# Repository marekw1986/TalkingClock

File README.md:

# TalkingClock

## Overwiev
This is repository of firmware for Talking Clock project. 
It uses vintage parts, such as WDC65C02 CPU, M6242B RTC, MC6840 timer or R65C51 UART. 
It also consists SP0256-AL2 chip, providing retro speach synthesis capability.

This project is still in development.

## Required tools
You need [cc65](https://github.com/cc65/cc65) to build this project.
Additionaly there are two PLD files, consisting descriptions of address decoders for GAL chips used in this project. 
To synthesise them you need [GalAsm](https://github.com/daveho/GALasm).

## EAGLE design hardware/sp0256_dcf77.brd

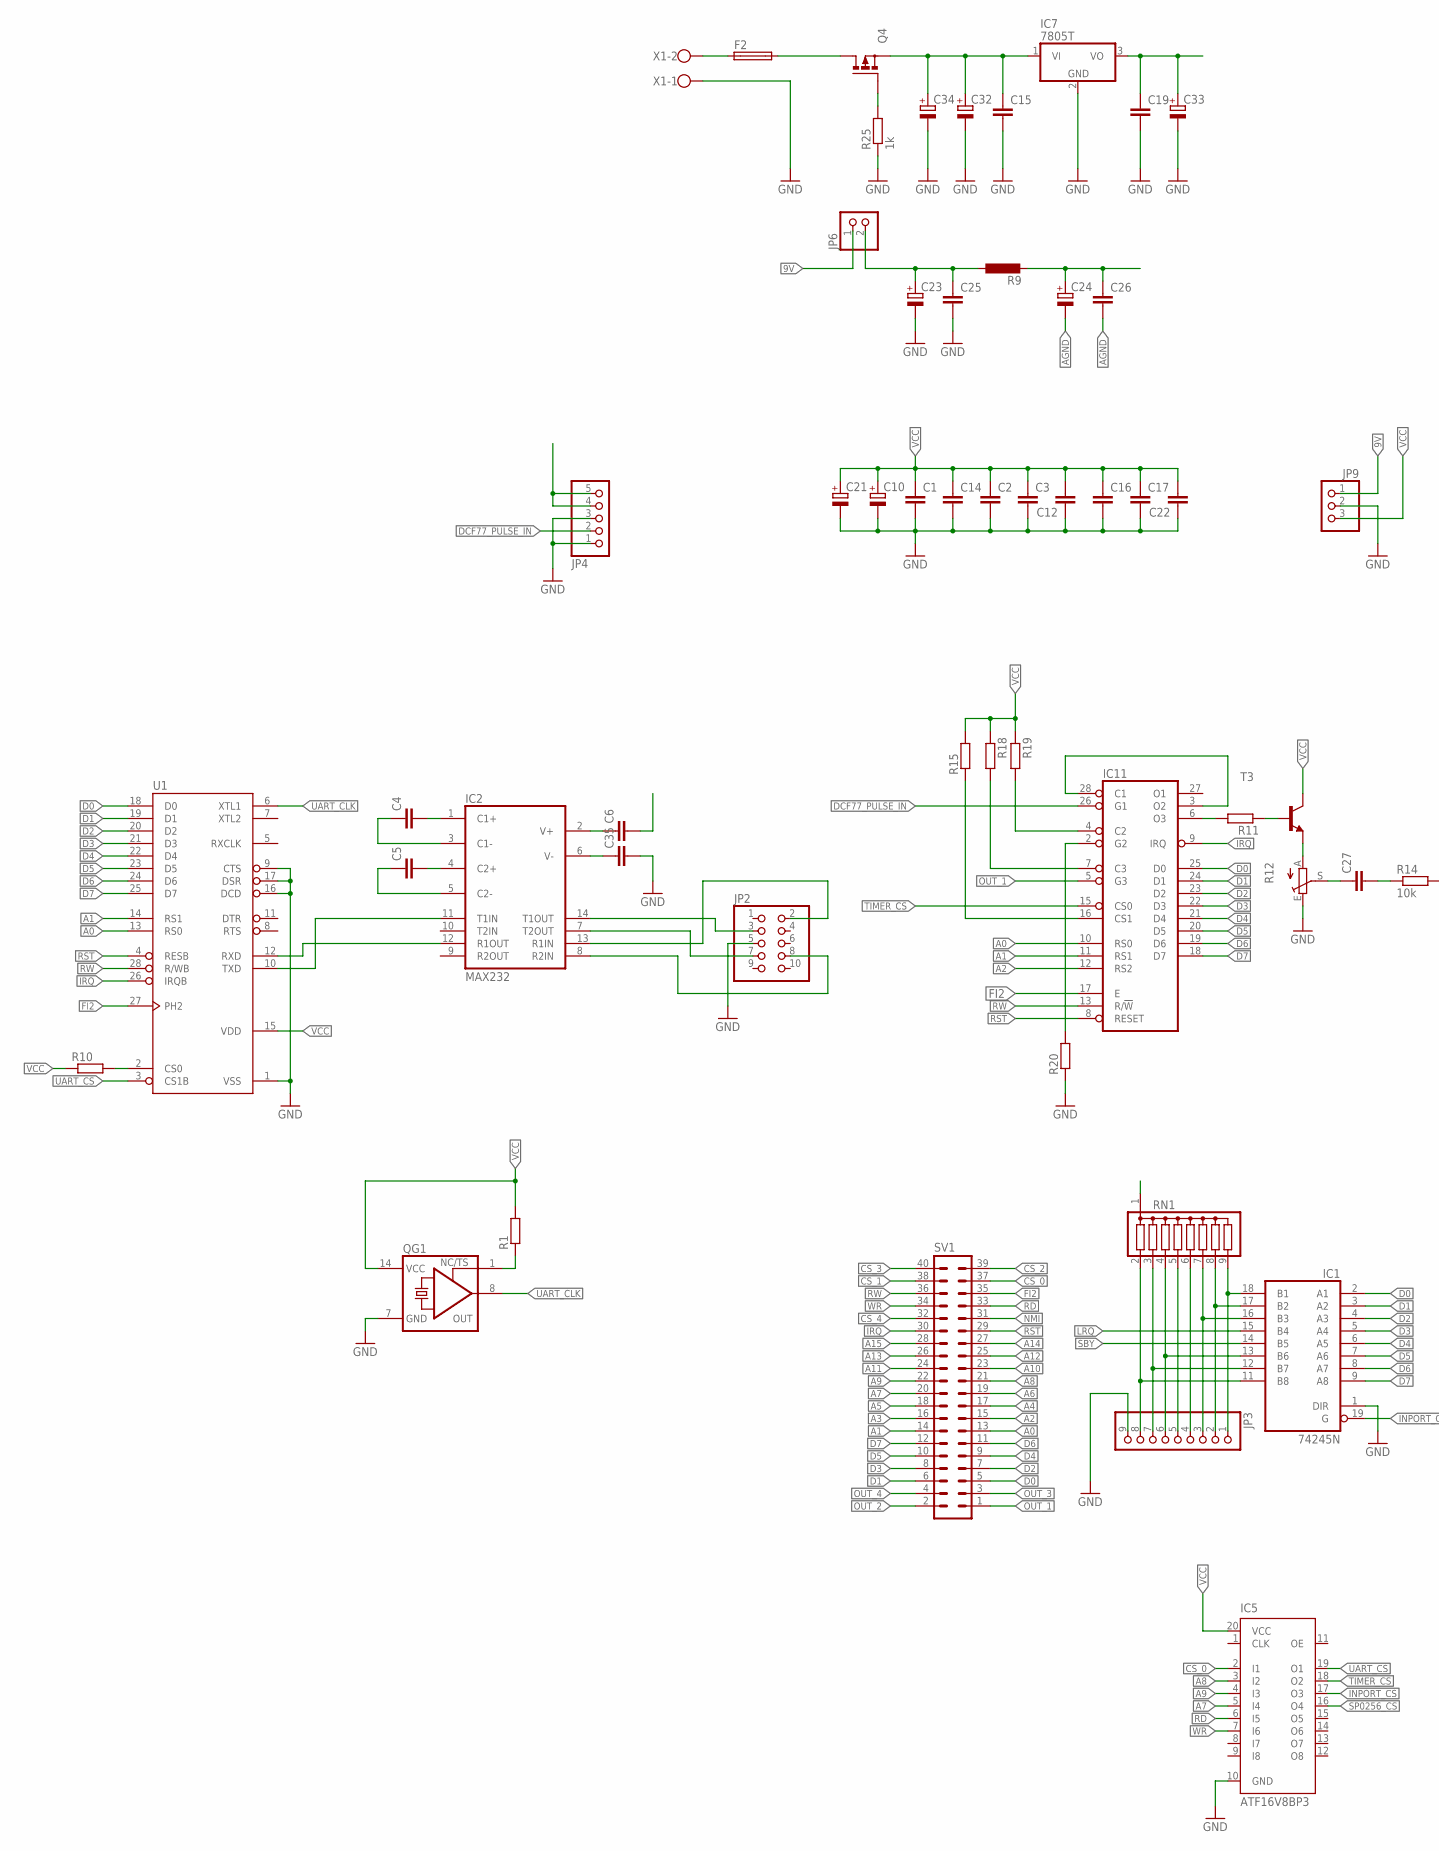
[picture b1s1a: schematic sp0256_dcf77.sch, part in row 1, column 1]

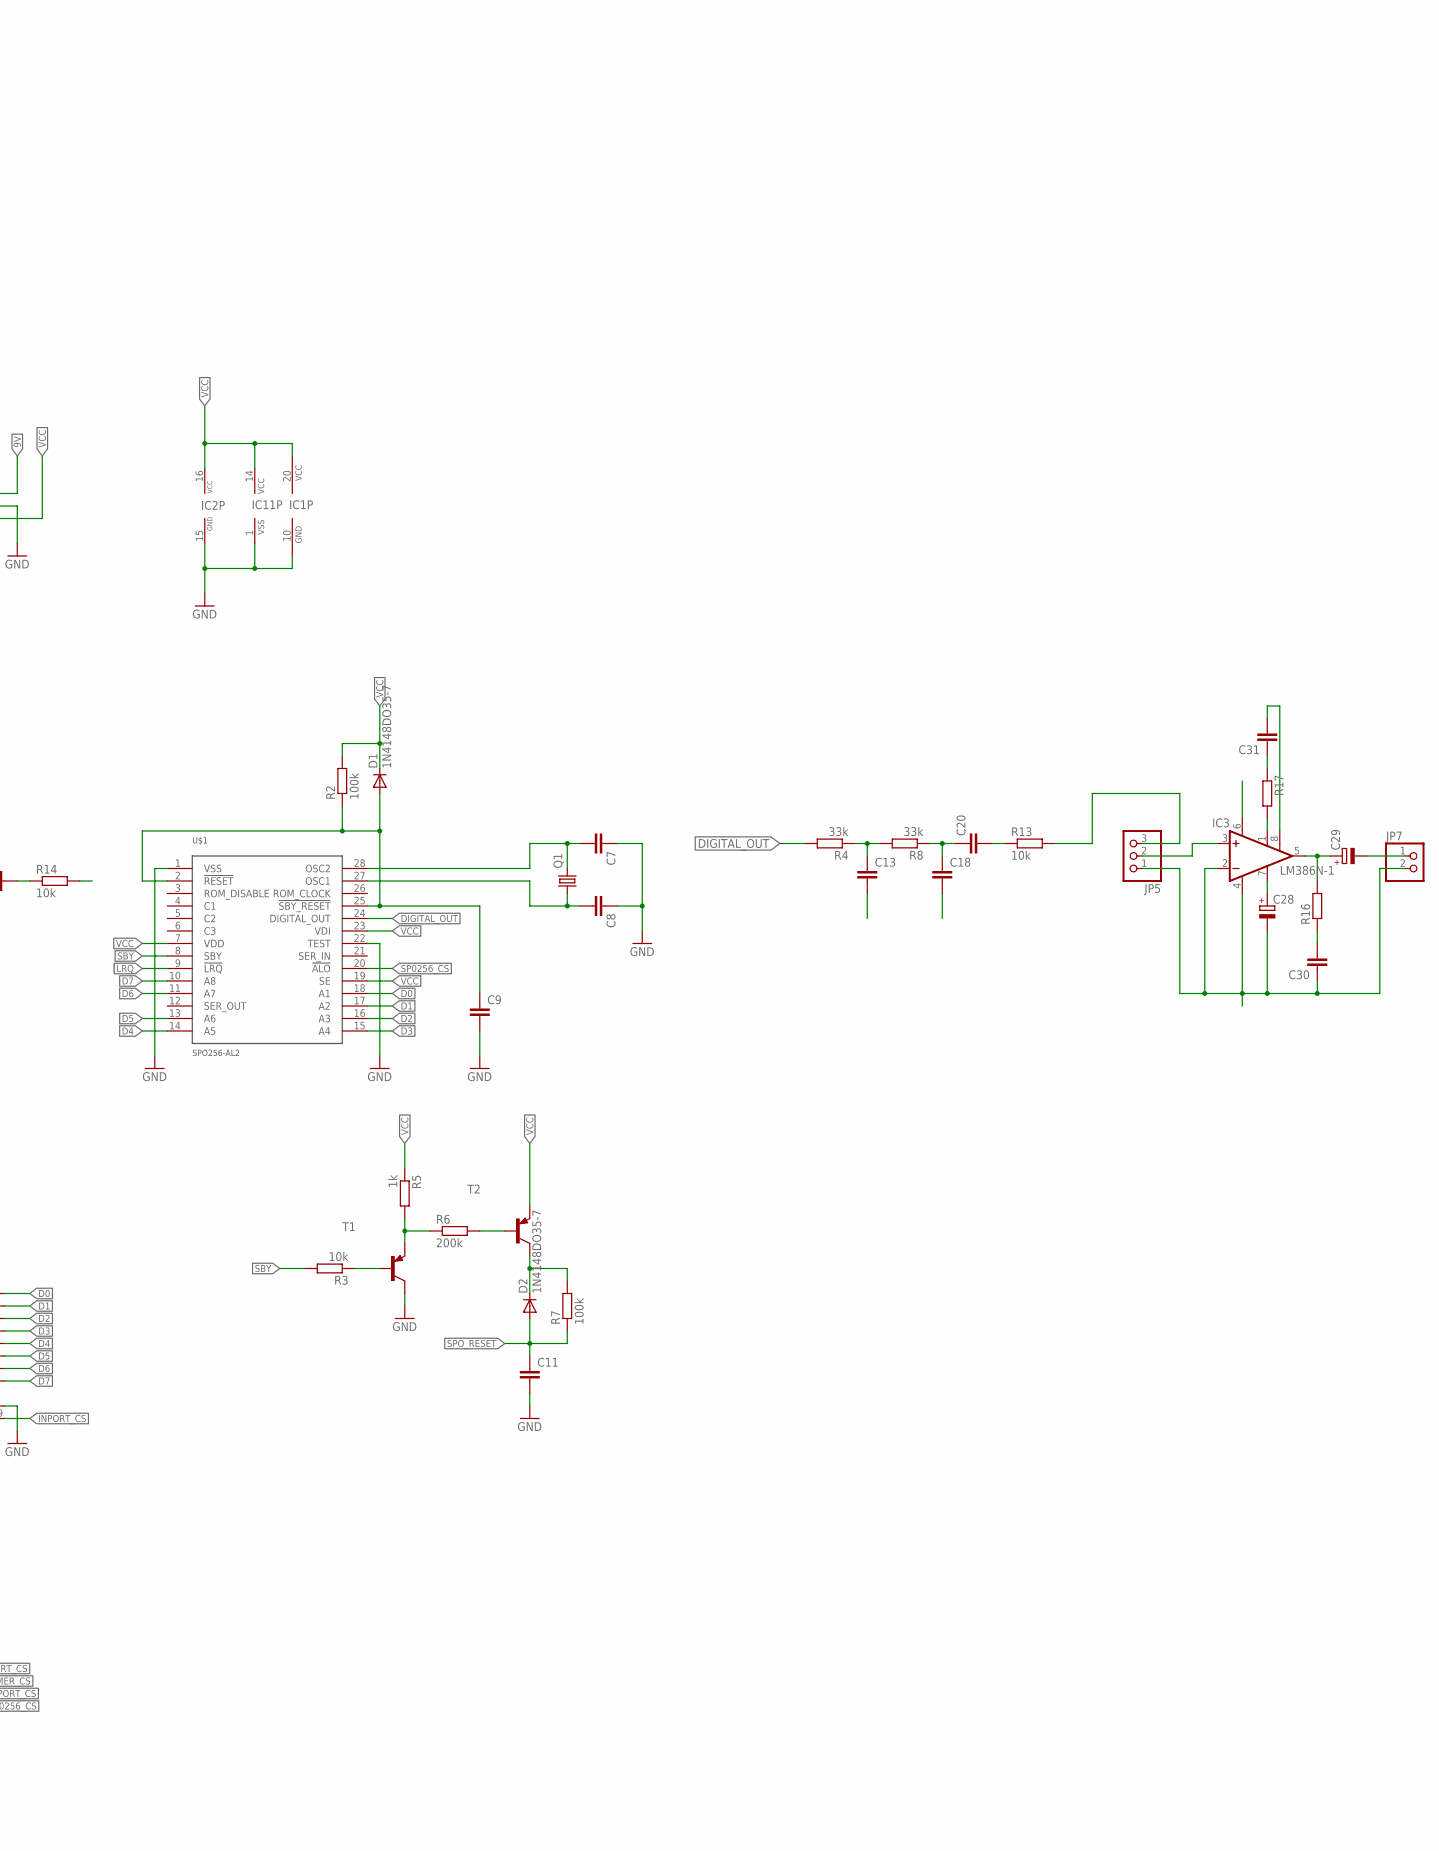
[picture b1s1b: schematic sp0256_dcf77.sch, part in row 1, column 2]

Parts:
C1, C2, C3, C14, C15, C16, C17, C19, C25, C26: C-EUC1206; C1206
C4, C5, C6, C7, C8, C9, C11, C12, C13, C18, C20, C22, C27, C30, C31, C35: C-EUC0603; C0603
C10, C23, C24, C29, C32, C33, C34: CPOL-EUE5-10.5; E5-10,5
C21, C28: CPOL-EUSMCB; SMC_B
D1, D2: 1N4148DO35-7; DO35-7
F2: SH22,5; MPN 0031.8201
IC1: 74245N; DIL20
IC2: MAX232; DIL16
IC3: LM386N-1; DIL08
IC5: ATF16V8BP3; DIL20
IC7: 7805T; TO220H
IC11: 6840; DIL28
JP2: PINHD-2X5; 2X05
JP3: PINHD-1X9; 1X09
JP4: PINHD-1X5; 1X05
JP5: PINHD-1X3; 1X03
JP6, JP7: PINHD-1X2; 1X02
JP9: PINHD-1X3/90; 1X03/90
Q1: CRYSTALHC49U-V; HC49U-V
Q4: P-MOSFET-SO8; SO-08
QG1: XO-14; DIL14S
R1: R-EU_R1206; R1206
R2, R7: 100k; 0204/7
R3: 10k; 0204/7
R4, R8: 33k; 0204/7
R5: 1k; 0204/5
R6: 200k; R0603
R9: L-EU0204/7; 0204/7
R10, R15, R16, R18, R19, R20: R-EU_R0603; R0603
R11, R17: R-EU_0204/7; 0204/7
R12: TRIM_EU-CA6V; CA6V
R13, R14: 10k; R0603
R25: 1k; R0603
RN1: G08R; SIL9
SV1: ML40L
T1, T2: MPS2907A-PNP-TO92-CBE; TO92-CBE
T3: BC550-NPN-TO92-CBE; TO92-CBE
U1: G65SC51P; DIP-28
U$1: SPO256-AL2; DIL28
X1: W237-102

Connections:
9V: C15.1, C32.+, C34.+, IC7.1 (VI), JP6.1, JP9.1, Q4.1 (S), Q4.2 (S), Q4.3 (S)
9V_SW: C23.+, C25.1, JP6.2, R9.1
A0: IC11.10 (RS0), SV1.13, U1.13 (RS0)
A1: IC11.11 (RS1), SV1.14, U1.14 (RS1)
A2: IC11.12 (RS2), SV1.15
A3: SV1.16
A4: SV1.17
A5: SV1.18
A6: SV1.19
A7: IC5.5 (I4), SV1.20
A8: IC5.3 (I2), SV1.21
A9: IC5.4 (I3), SV1.22
A10: SV1.23
A11: SV1.24
A12: SV1.25
A13: SV1.26
A14: SV1.27
A15: SV1.28
AGND: C13.2, C18.2, C24.-, C26.2, C28.-, C30.1, IC3.2 (-IN), IC3.4 (GND), JP5.1, JP7.2
AUDIO_AMP_IN: JP5.3, R13.2, R14.2
AVCC: C24.+, C26.1, IC3.6 (VS), R9.2
CS_0: IC5.2 (I1), SV1.37
CS_1: SV1.38
CS_2: SV1.39
CS_3: SV1.40
CS_4: SV1.32
D0: IC1.2 (A1), IC11.25 (D0), SV1.5, U1.18 (D0), U$1.18 (A1)
D1: IC1.3 (A2), IC11.24 (D1), SV1.6, U1.19 (D1), U$1.17 (A2)
D2: IC1.4 (A3), IC11.23 (D2), SV1.7, U1.20 (D2), U$1.16 (A3)
D3: IC1.5 (A4), IC11.22 (D3), SV1.8, U1.21 (D3), U$1.15 (A4)
D4: IC1.6 (A5), IC11.21 (D4), SV1.9, U1.22 (D4), U$1.14 (A5)
D5: IC1.7 (A6), IC11.20 (D5), SV1.10, U1.23 (D5), U$1.13 (A6)
D6: IC1.8 (A7), IC11.19 (D6), SV1.11, U1.24 (D6), U$1.11 (A7)
D7: IC1.9 (A8), IC11.18 (D7), SV1.12, U1.25 (D7), U$1.10 (A8)
DIGITAL_OUT: R4.2, U$1.24 (DIGITAL_OUT)
FI2: IC11.17 (E), SV1.35, U1.27 (PH2)
GATE2: IC11.2 (G2), R20.2
GND: C1.2, C2.2, C3.2, C7.1, C8.1, C9.2, C10.-, C11.2, C12.1, C14.2, C15.2, C16.2, C17.2, C19.2, C21.-, C22.1, C23.-, C25.2, C32.-, C33.-, C34.-, C35.2, IC1.1 (DIR), IC1.10 (GND), IC2.15 (GND), IC5.10 (GND), IC7.2 (GND), IC11.1 (VSS), JP2.5, JP3.9, JP4.1, JP4.3, JP9.2, QG1.7 (GND), R12.E, R20.1, R25.1, T1.C, U1.1 (VSS), U1.9 (CTS), U1.16 (DCD), U1.17 (DSR), U$1.1 (VSS), U$1.22 (TEST), X1.1
INPORT_CS: IC1.19 (G), IC5.17 (O3)
IRQ: IC11.9 (IRQ), SV1.30, U1.26 (IRQB)
LRQ: IC1.15 (B4), U$1.9 (!LRQ)
unnamed: Q4.4 (G), R25.2
unnamed: IC11.3 (O2), IC11.28 (C1)
unnamed: C35.1, IC2.6 (V-)
unnamed: QG1.1 (TS), R1.1
unnamed: C7.2, Q1.2, U$1.28 (OSC2)
unnamed: C8.2, Q1.1, U$1.27 (OSC1)
unnamed: R3.1, T1.B
unnamed: C4.2, IC2.1 (C1+)
unnamed: C5.2, IC2.4 (C2+)
unnamed: C5.1, IC2.5 (C2-)
unnamed: C4.1, IC2.3 (C1-)
unnamed: C6.1, IC2.2 (V+)
unnamed: IC1.18 (B1), JP3.1, RN1.9
unnamed: IC1.17 (B2), JP3.2, RN1.8
unnamed: IC1.16 (B3), JP3.3, RN1.7
unnamed: C13.1, R4.1, R8.2
unnamed: JP3.5, RN1.5
unnamed: IC1.13 (B6), JP3.6, RN1.4
unnamed: IC1.12 (B7), JP3.7, RN1.3
unnamed: IC1.11 (B8), JP3.8, RN1.2
unnamed: JP3.4, RN1.6
unnamed: R10.2, U1.2 (CS0)
unnamed: R5.2, R6.1, T1.E
unnamed: R6.2, T2.B
unnamed: D2.C, R7.2, T2.C
unnamed: IC11.16 (CS1), R15.1
unnamed: C18.1, C20.1, R8.1
unnamed: C28.+, IC3.7 (BYPASS)
unnamed: IC11.7 (C3), R18.2
unnamed: IC11.6 (O3), R11.2
unnamed: R11.1, T3.B
unnamed: R12.A, T3.E
unnamed: C27.1, R12.S
unnamed: C27.2, R14.1
unnamed: C20.2, R13.1
unnamed: IC3.3 (+IN), JP5.2
unnamed: C29.+, IC3.5 (OUT), R16.2
unnamed: C30.2, R16.1
unnamed: IC3.1 (GAIN), R17.2
unnamed: C31.1, R17.1
unnamed: C31.2, IC3.8 (GAIN)
unnamed: C29.-, JP7.1
unnamed: IC11.4 (C2), R19.2
unnamed: F2.2, Q4.5 (D), Q4.6 (D), Q4.7 (D), Q4.8 (D)
unnamed: F2.1, X1.2
NMI: SV1.31
OUT_1: IC11.5 (G3), SV1.1
OUT_2: SV1.2
OUT_3: SV1.3
OUT_4: SV1.4
RD: IC5.6 (I5), SV1.33
RST: IC11.8 (RESET), SV1.29, U1.4 (RESB)
RS_CTS: IC2.8 (R2IN), JP2.8
RS_RTS: IC2.7 (T2OUT), JP2.7
RS_RXD: IC2.13 (R1IN), JP2.2
RS_TXD: IC2.14 (T1OUT), JP2.3
RW: IC11.13 (R/!W), SV1.36, U1.28 (R/WB)
RXD_TTL: IC2.12 (R1OUT), U1.12 (RXD)
SBY: IC1.14 (B5), R3.2, U$1.8 (SBY)
SP0256_CS: IC5.16 (O4), U$1.20 (!ALO)
SPO_RESET: C9.1, C11.1, D1.A, D2.A, R2.1, R7.1, U$1.2 (!RESET), U$1.25 (!SBY_RESET)
TIMER_CS: IC5.18 (O2), IC11.15 (CS0)
TXD_TTL: IC2.11 (T1IN), U1.10 (TXD)
UART_CLK: QG1.8 (OUT), U1.6 (XTL1)
UART_CS: IC5.19 (O1), U1.3 (CS1B)
VCC: C1.1, C2.1, C3.1, C6.2, C10.+, C12.2, C14.1, C16.1, C17.1, C19.1, C21.+, C22.2, C33.+, D1.C, IC1.20 (VCC), IC2.16 (VCC), IC5.20 (VCC), IC7.3 (VO), IC11.14 (VCC), JP4.4, JP4.5, JP9.3, QG1.14 (VCC), R1.2, R2.2, R5.1, R10.1, R15.2, R18.1, R19.1, RN1.1, T2.E, T3.C, U1.15 (VDD), U$1.7 (VDD), U$1.19 (SE), U$1.23 (VDI)
WR: IC5.7 (I6), SV1.34

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
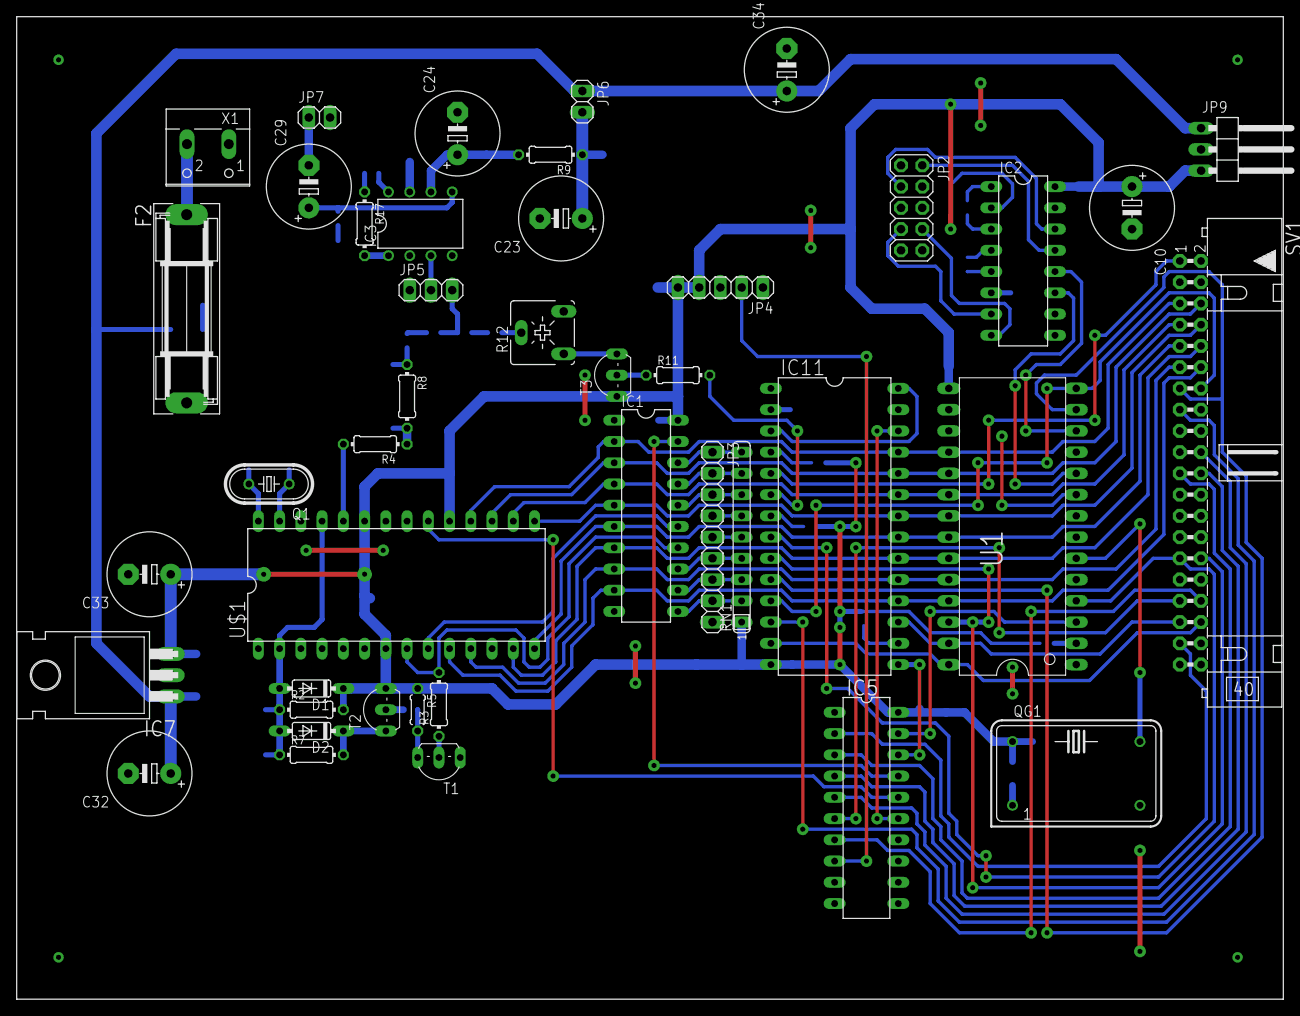
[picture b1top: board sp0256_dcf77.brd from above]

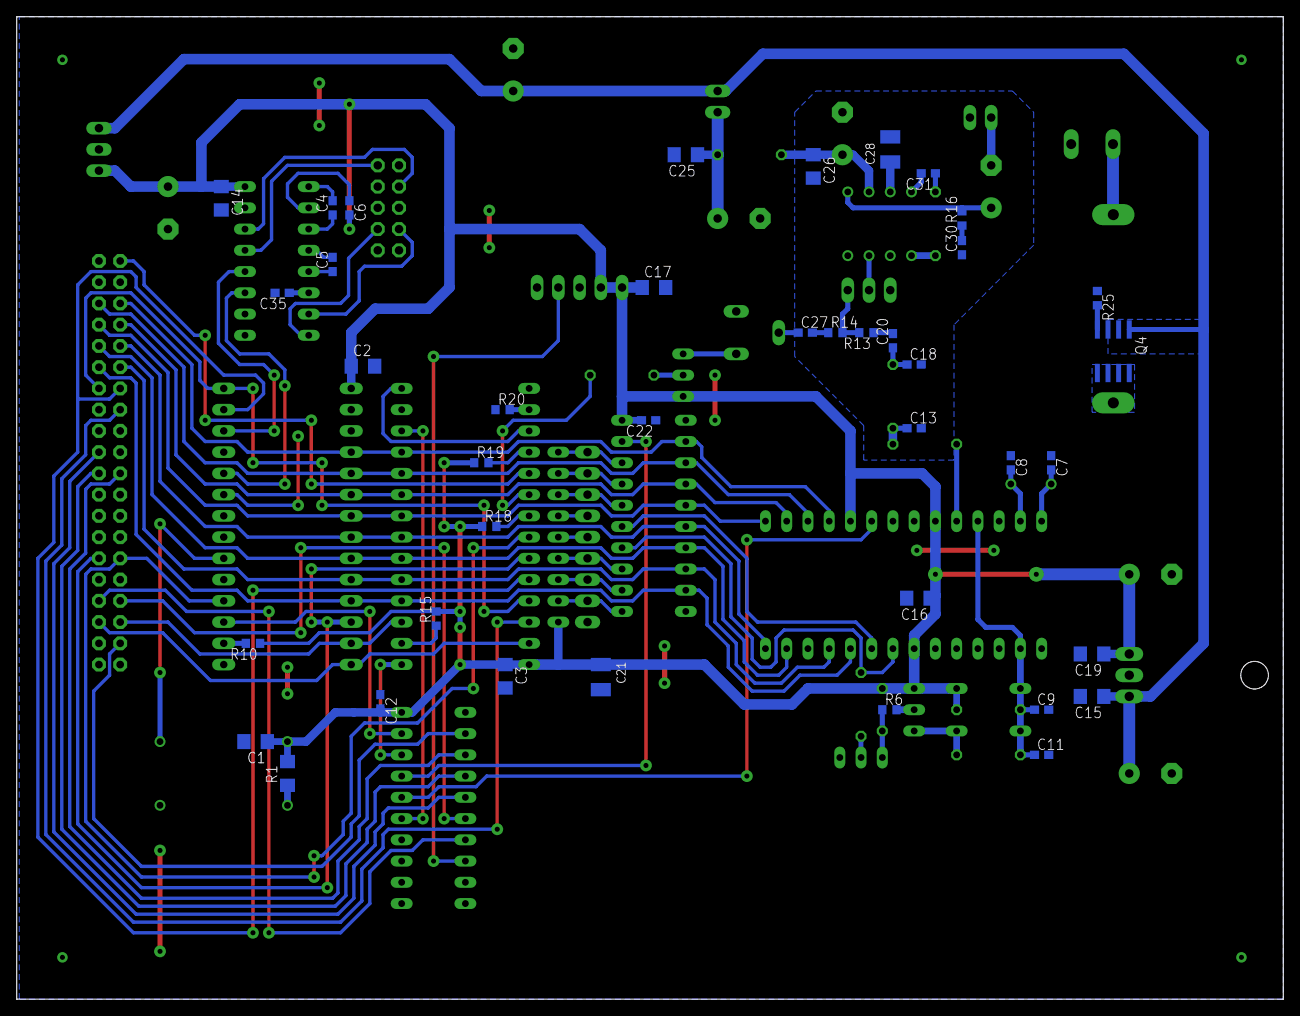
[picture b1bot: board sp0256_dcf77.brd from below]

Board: 2 copper layers, 151.4 x 117.5 mm, 83 parts (40 on the bottom side), 92 nets.

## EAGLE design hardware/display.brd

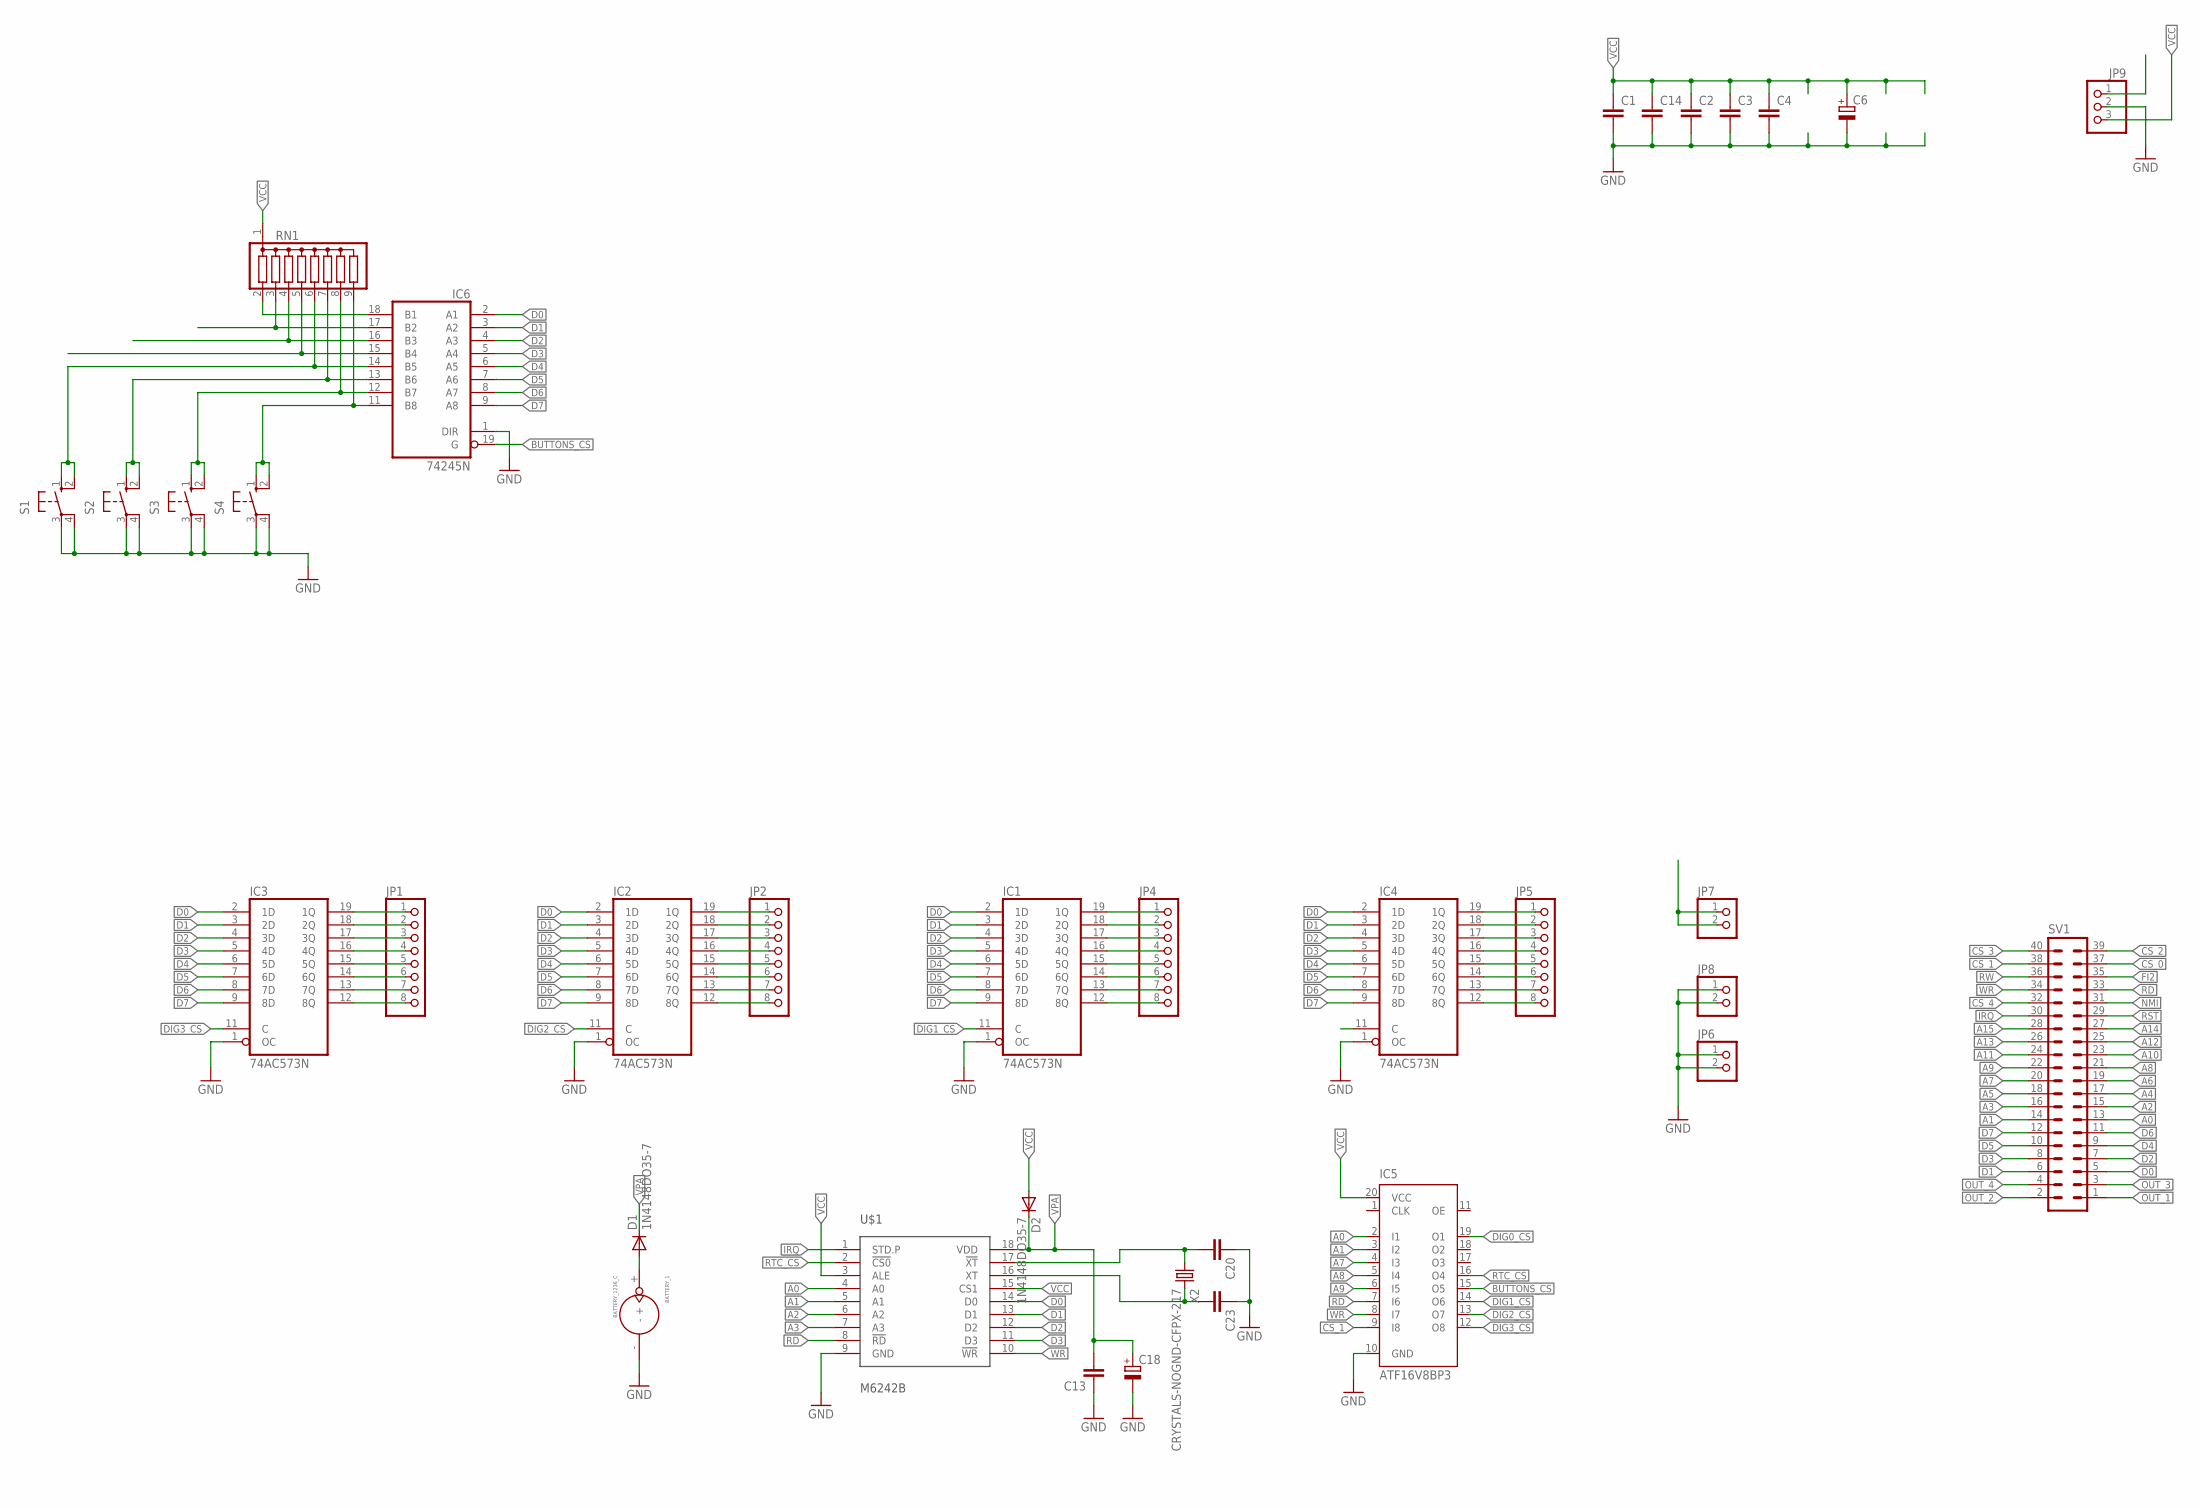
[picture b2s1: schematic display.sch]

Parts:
BATTERY_1: BATTERY_1236_C
C1, C2, C3, C4, C14: C-EUC1206; C1206
C6: CPOL-EUSMCD; SMC_D
C13, C20, C23: C-EUC0603; C0603
C18: CPOL-EUSMCB; SMC_B
D1, D2: 1N4148DO35-7; DO35-7
IC1, IC2, IC3, IC4: 74AC573N; DIL20
IC5: ATF16V8BP3; DIL20
IC6: 74245N; DIL20
JP1, JP2, JP4, JP5: PINHD-1X8; 1X08
JP6, JP7, JP8: PINHD-1X2; 1X02
JP9: PINHD-1X3/90; 1X03/90
RN1: G08R; SIL9
S1, S2, S3, S4: 40-XX; B3F-40XX
SV1: ML40L
U$1: M6242B; DIL18
X2: CRYSTALS-NOGND-CFPX-217; 3.2X1.5-2-PAD

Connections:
9V: JP7.1, JP7.2, JP9.1
A0: IC5.2 (I1), SV1.13, U$1.4 (A0)
A1: IC5.3 (I2), SV1.14, U$1.5 (A1)
A2: SV1.15, U$1.6 (A2)
A3: SV1.16, U$1.7 (A3)
A4: SV1.17
A5: SV1.18
A6: SV1.19
A7: IC5.4 (I3), SV1.20
A8: IC5.5 (I4), SV1.21
A9: IC5.6 (I5), SV1.22
A10: SV1.23
A11: SV1.24
A12: SV1.25
A13: SV1.26
A14: SV1.27
A15: SV1.28
BUTTONS_CS: IC5.15 (O5), IC6.19 (G)
CS_0: SV1.37
CS_1: IC5.9 (I8), SV1.38
CS_2: SV1.39
CS_3: SV1.40
CS_4: SV1.32
D0: IC1.2 (1D), IC2.2 (1D), IC3.2 (1D), IC4.2 (1D), IC6.2 (A1), SV1.5, U$1.14 (D0)
D1: IC1.3 (2D), IC2.3 (2D), IC3.3 (2D), IC4.3 (2D), IC6.3 (A2), SV1.6, U$1.13 (D1)
D2: IC1.4 (3D), IC2.4 (3D), IC3.4 (3D), IC4.4 (3D), IC6.4 (A3), SV1.7, U$1.12 (D2)
D3: IC1.5 (4D), IC2.5 (4D), IC3.5 (4D), IC4.5 (4D), IC6.5 (A4), SV1.8, U$1.11 (D3)
D4: IC1.6 (5D), IC2.6 (5D), IC3.6 (5D), IC4.6 (5D), IC6.6 (A5), SV1.9
D5: IC1.7 (6D), IC2.7 (6D), IC3.7 (6D), IC4.7 (6D), IC6.7 (A6), SV1.10
D6: IC1.8 (7D), IC2.8 (7D), IC3.8 (7D), IC4.8 (7D), IC6.8 (A7), SV1.11
D7: IC1.9 (8D), IC2.9 (8D), IC3.9 (8D), IC4.9 (8D), IC6.9 (A8), SV1.12
DIG0_CS: IC4.11 (C), IC5.19 (O1)
DIG1_CS: IC1.11 (C), IC5.14 (O6)
DIG2_CS: IC2.11 (C), IC5.13 (O7)
DIG3_CS: IC3.11 (C), IC5.12 (O8)
FI2: SV1.35
GND: BATTERY_1.-, C1.2, C2.2, C3.2, C4.2, C6.-, C13.1, C14.2, C18.-, C20.1, C23.1, IC1.1 (OC), IC1.10 (GND), IC2.1 (OC), IC2.10 (GND), IC3.1 (OC), IC3.10 (GND), IC4.1 (OC), IC4.10 (GND), IC5.10 (GND), IC6.1 (DIR), IC6.10 (GND), JP6.1, JP6.2, JP8.1, JP8.2, JP9.2, S1.3, S1.4 (P1), S2.3, S2.4 (P1), S3.3, S3.4 (P1), S4.3, S4.4 (P1), U$1.9 (GND)
IRQ: SV1.30, U$1.1 (STD.P)
unnamed: IC3.12 (8Q), JP1.8
unnamed: IC3.13 (7Q), JP1.7
unnamed: IC3.14 (6Q), JP1.6
unnamed: IC3.19 (1Q), JP1.1
unnamed: IC3.18 (2Q), JP1.2
unnamed: IC3.17 (3Q), JP1.3
unnamed: IC3.16 (4Q), JP1.4
unnamed: IC3.15 (5Q), JP1.5
unnamed: IC2.17 (3Q), JP2.3
unnamed: IC2.18 (2Q), JP2.2
unnamed: IC2.19 (1Q), JP2.1
unnamed: IC2.16 (4Q), JP2.4
unnamed: IC2.15 (5Q), JP2.5
unnamed: IC2.14 (6Q), JP2.6
unnamed: IC2.13 (7Q), JP2.7
unnamed: IC2.12 (8Q), JP2.8
unnamed: IC1.19 (1Q), JP4.1
unnamed: IC1.18 (2Q), JP4.2
unnamed: IC1.17 (3Q), JP4.3
unnamed: IC1.16 (4Q), JP4.4
unnamed: IC1.15 (5Q), JP4.5
unnamed: IC1.14 (6Q), JP4.6
unnamed: IC1.13 (7Q), JP4.7
unnamed: IC1.12 (8Q), JP4.8
unnamed: IC4.17 (3Q), JP5.3
unnamed: IC4.19 (1Q), JP5.1
unnamed: IC4.18 (2Q), JP5.2
unnamed: IC4.16 (4Q), JP5.4
unnamed: IC4.15 (5Q), JP5.5
unnamed: IC4.14 (6Q), JP5.6
unnamed: IC4.13 (7Q), JP5.7
unnamed: IC4.12 (8Q), JP5.8
unnamed: BATTERY_1.+, D1.A
unnamed: IC6.14 (B5), RN1.6, S1.1 (S), S1.2 (S1)
unnamed: IC6.13 (B6), RN1.7, S2.1 (S), S2.2 (S1)
unnamed: IC6.12 (B7), RN1.8, S3.1 (S), S3.2 (S1)
unnamed: IC6.11 (B8), RN1.9, S4.1 (S), S4.2 (S1)
NMI: SV1.31
OUT_1: SV1.1
OUT_2: SV1.2
OUT_3: SV1.3
OUT_4: SV1.4
RD: IC5.7 (I6), SV1.33, U$1.8 (!RD)
RST: SV1.29
RTC_CS: IC5.16 (O4), U$1.2 (!CS0)
RW: SV1.36
S1: IC6.15 (B4), RN1.5
S2: IC6.16 (B3), RN1.4
S3: IC6.17 (B2), RN1.3
S4: IC6.18 (B1), RN1.2
SOSCI: C20.2, U$1.17 (!XT), X2.1
SOSCO: C23.2, U$1.16 (XT), X2.2
VCC: C1.1, C2.1, C3.1, C4.1, C6.+, C14.1, D2.A, IC1.20 (VCC), IC2.20 (VCC), IC3.20 (VCC), IC4.20 (VCC), IC5.20 (VCC), IC6.20 (VCC), JP9.3, RN1.1, U$1.3 (ALE), U$1.15 (CS1)
VPA: C13.2, C18.+, D1.C, D2.C, U$1.18 (VDD)
WR: IC5.8 (I7), SV1.34, U$1.10 (!WR)

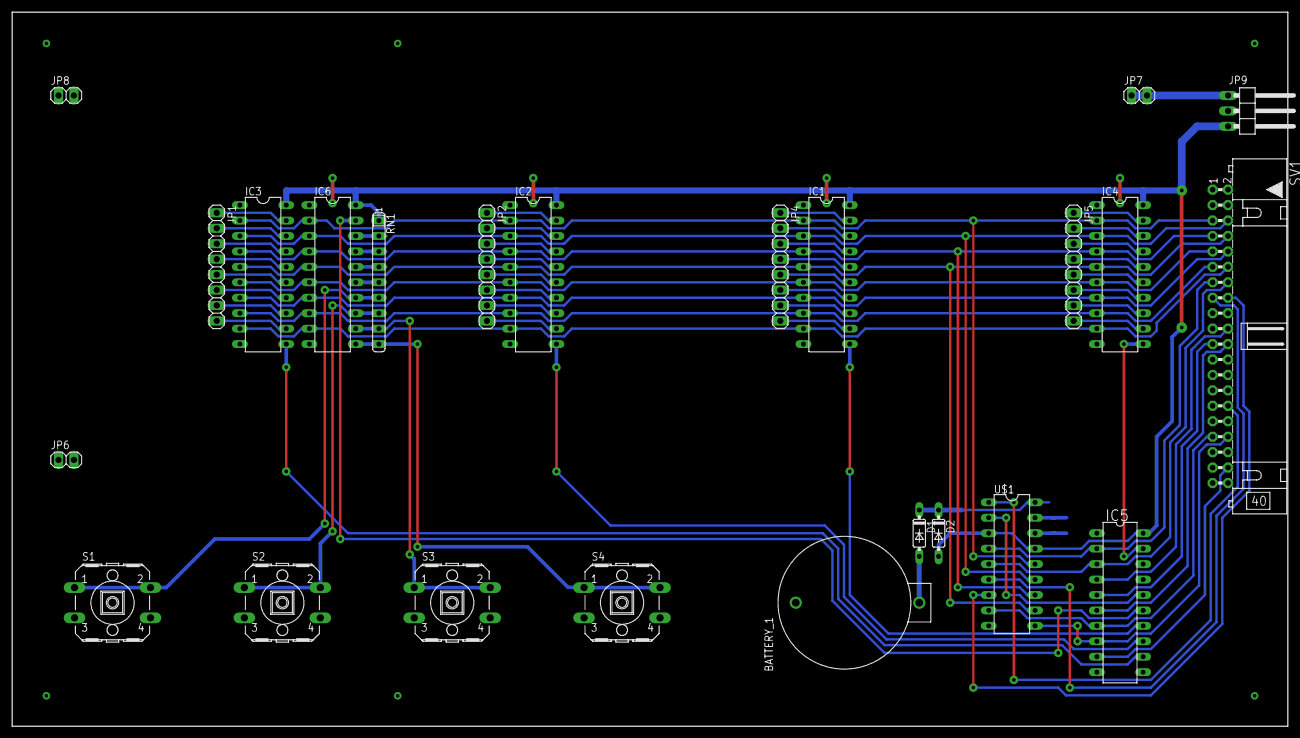
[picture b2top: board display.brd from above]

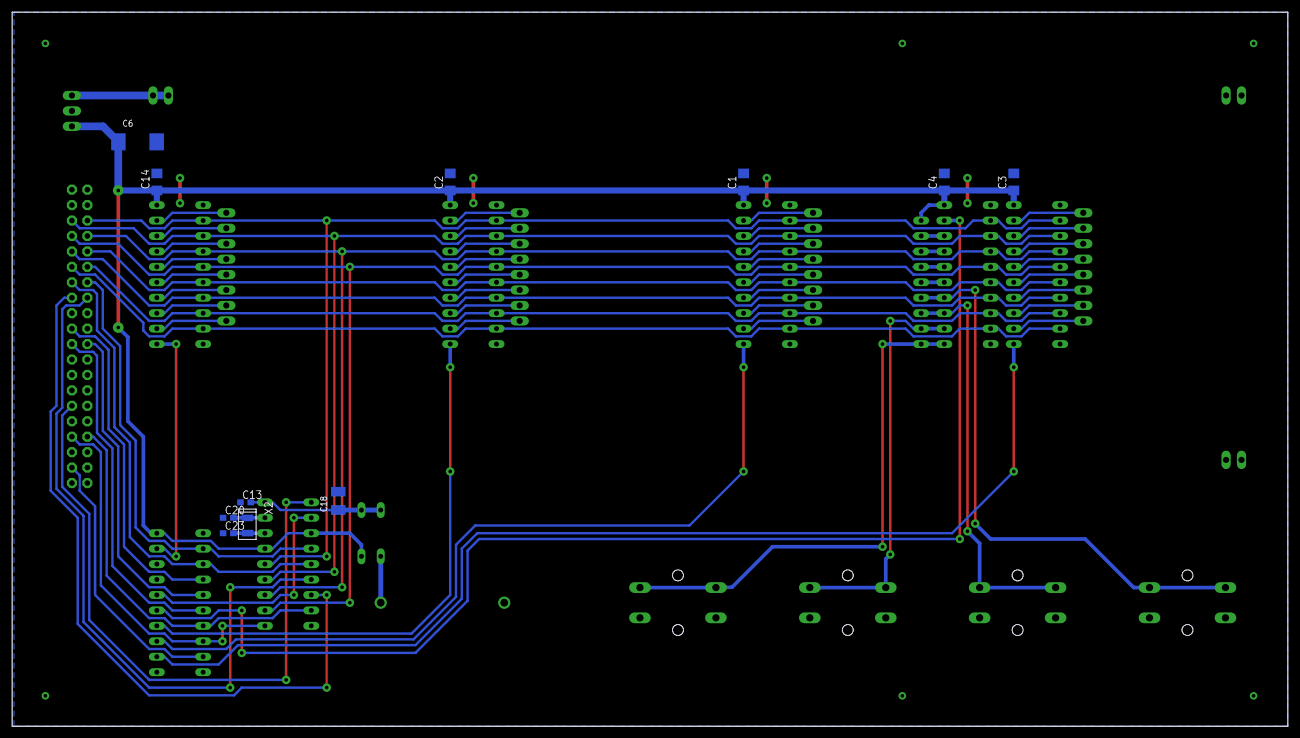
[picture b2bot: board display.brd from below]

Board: 2 copper layers, 209.9 x 117.5 mm, 35 parts (11 on the bottom side), 72 nets.

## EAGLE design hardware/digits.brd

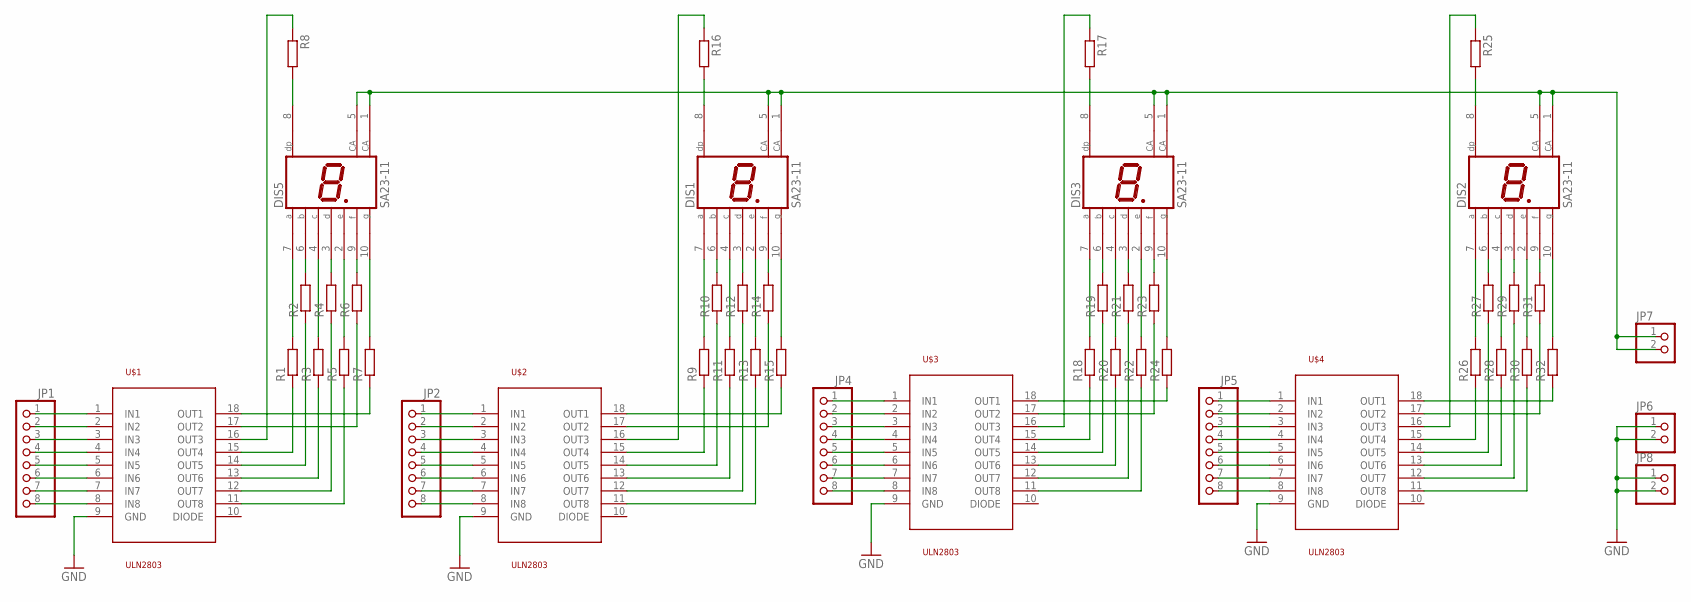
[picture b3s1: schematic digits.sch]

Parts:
DIS1, DIS2, DIS3, DIS5: SA23-11; SX23-XX
JP1, JP2, JP4, JP5: PINHD-1X8; 1X08
JP6, JP7, JP8: PINHD-1X2; 1X02
R1, R2, R6, R7, R8, R9, R10, R14, R15, R16, R17, R18, R19, R23, R24, R25, R26, R27, R31, R32: R-EU_R0603; R0603
R3, R4, R5, R11, R12, R13, R20, R21, R22, R28, R29, R30: R-EU_0204/7; 0204/7
U$1, U$2, U$3, U$4: ULN2803; SO18L

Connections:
9V: DIS1.1 (CA), DIS1.5 (CA), DIS2.1 (CA), DIS2.5 (CA), DIS3.1 (CA), DIS3.5 (CA), DIS5.1 (CA), DIS5.5 (CA), JP7.1, JP7.2
GND: JP6.1, JP6.2, JP8.1, JP8.2, U$1.9 (GND), U$2.9 (GND), U$3.9 (GND), U$4.9 (GND)
unnamed: DIS5.7 (A), R1.2
unnamed: DIS5.6 (B), R2.2
unnamed: JP1.8, U$1.8 (IN8)
unnamed: JP1.7, U$1.7 (IN7)
unnamed: JP1.6, U$1.6 (IN6)
unnamed: JP1.1, U$1.1 (IN1)
unnamed: JP1.2, U$1.2 (IN2)
unnamed: JP1.3, U$1.3 (IN3)
unnamed: JP1.4, U$1.4 (IN4)
unnamed: JP1.5, U$1.5 (IN5)
unnamed: DIS5.4 (C), R3.2
unnamed: DIS5.3 (D), R4.2
unnamed: DIS5.2 (E), R5.2
unnamed: DIS5.9 (F), R6.2
unnamed: DIS5.10 (G), R7.2
unnamed: DIS5.8 (DP), R8.2
unnamed: DIS1.7 (A), R9.2
unnamed: DIS1.4 (C), R11.2
unnamed: DIS1.2 (E), R13.2
unnamed: DIS1.10 (G), R15.2
unnamed: DIS1.6 (B), R10.2
unnamed: DIS1.3 (D), R12.2
unnamed: DIS1.9 (F), R14.2
unnamed: DIS1.8 (DP), R16.2
unnamed: DIS3.8 (DP), R17.2
unnamed: DIS3.7 (A), R18.2
unnamed: DIS3.4 (C), R20.2
unnamed: JP2.3, U$2.3 (IN3)
unnamed: JP2.2, U$2.2 (IN2)
unnamed: JP2.1, U$2.1 (IN1)
unnamed: JP2.4, U$2.4 (IN4)
unnamed: JP2.5, U$2.5 (IN5)
unnamed: JP2.6, U$2.6 (IN6)
unnamed: JP2.7, U$2.7 (IN7)
unnamed: JP2.8, U$2.8 (IN8)
unnamed: JP4.1, U$3.1 (IN1)
unnamed: DIS3.2 (E), R22.2
unnamed: JP4.2, U$3.2 (IN2)
unnamed: JP4.3, U$3.3 (IN3)
unnamed: DIS3.10 (G), R24.2
unnamed: DIS3.6 (B), R19.2
unnamed: DIS3.3 (D), R21.2
unnamed: DIS3.9 (F), R23.2
unnamed: DIS2.8 (DP), R25.2
unnamed: DIS2.7 (A), R26.2
unnamed: DIS2.4 (C), R28.2
unnamed: DIS2.2 (E), R30.2
unnamed: JP4.4, U$3.4 (IN4)
unnamed: JP4.5, U$3.5 (IN5)
unnamed: JP4.6, U$3.6 (IN6)
unnamed: JP4.7, U$3.7 (IN7)
unnamed: JP4.8, U$3.8 (IN8)
unnamed: DIS2.10 (G), R32.2
unnamed: DIS2.6 (B), R27.2
unnamed: DIS2.3 (D), R29.2
unnamed: DIS2.9 (F), R31.2
unnamed: R5.1, U$1.11 (OUT8)
unnamed: R4.1, U$1.12 (OUT7)
unnamed: R3.1, U$1.13 (OUT6)
unnamed: R2.1, U$1.14 (OUT5)
unnamed: JP5.3, U$4.3 (IN3)
unnamed: JP5.1, U$4.1 (IN1)
unnamed: JP5.2, U$4.2 (IN2)
unnamed: JP5.4, U$4.4 (IN4)
unnamed: JP5.5, U$4.5 (IN5)
unnamed: JP5.6, U$4.6 (IN6)
unnamed: JP5.7, U$4.7 (IN7)
unnamed: JP5.8, U$4.8 (IN8)
unnamed: R1.1, U$1.15 (OUT4)
unnamed: R8.1, U$1.16 (OUT3)
unnamed: R6.1, U$1.17 (OUT2)
unnamed: R7.1, U$1.18 (OUT1)
unnamed: R15.1, U$2.18 (OUT1)
unnamed: R14.1, U$2.17 (OUT2)
unnamed: R16.1, U$2.16 (OUT3)
unnamed: R9.1, U$2.15 (OUT4)
unnamed: R10.1, U$2.14 (OUT5)
unnamed: R11.1, U$2.13 (OUT6)
unnamed: R12.1, U$2.12 (OUT7)
unnamed: R13.1, U$2.11 (OUT8)
unnamed: R24.1, U$3.18 (OUT1)
unnamed: R23.1, U$3.17 (OUT2)
unnamed: R17.1, U$3.16 (OUT3)
unnamed: R18.1, U$3.15 (OUT4)
unnamed: R19.1, U$3.14 (OUT5)
unnamed: R20.1, U$3.13 (OUT6)
unnamed: R21.1, U$3.12 (OUT7)
unnamed: R22.1, U$3.11 (OUT8)
unnamed: R32.1, U$4.18 (OUT1)
unnamed: R31.1, U$4.17 (OUT2)
unnamed: R25.1, U$4.16 (OUT3)
unnamed: R26.1, U$4.15 (OUT4)
unnamed: R27.1, U$4.14 (OUT5)
unnamed: R28.1, U$4.13 (OUT6)
unnamed: R29.1, U$4.12 (OUT7)
unnamed: R30.1, U$4.11 (OUT8)

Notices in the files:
parts and their libraries:
SparkFun: Licensing: CC v3.0 Share-Alike You are welcome to use this library for commercial purposes.
SparkFun-Aesthetics: Licensing: Creative Commons ShareAlike 4.0 International - https://creativecommons.org/licenses/by-sa/4.0
